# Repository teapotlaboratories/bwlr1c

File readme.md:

# Teapotlabs BWLR1C

Teapotlabs BWLR1C is a wireless LoRa environmental sensor capable of sensing temperature, humidity, air pressure and air quality using the on-board BME680.
This device is an updated to **Teapotlabs BWLR1B,** by using the an on-board antenna.
By using an STM32WLE MCU, the device is capable of multi-year operation before changing the batteries

Teapotlabs BWLR1C is part of  [Teapot open-hardware project](https://github.com/teapotlaboratories).

## Sponsorship
Huge thanks to [PCBWay](https://www.pcbway.com/) to sponsored this project! Most of the project in Teapotlabs from PCB board, PCB Assembly, and 3D Printing is done through their rapid-prototyping services. The process from ordering to delivery of the device was really smooth and easy. We were really happy with the quality of the assembly and especially the customer support that was really easy to work with, where they help us identify and fix issue such as verifying BOM, checking components for assembly and even replacing damaged parts at no cost.

## Disclaimer
- The 1KM range is based on [AERQ - Air Quality Monitoring](https://www.seeedstudio.com/blog/2022/04/27/monitoring-indoor-air-pollutants-the-silent-issue-for-smart-city-iot-using-seeed-lora-e5-and-fusion-pcba/) design, but have not been tested on this device yet
- The position of the BME680 sensor on the board might not be the most efficient

## Future Works
- Change `SW4` wiring from GND to 3V3, to allow booting to STM32WLE USART Bootloader. This enable the user to flash the RAK3172 module using STM32CubeProgrammer without ST-Link.

## Specification

- [RAK3172](https://docs.rakwireless.com/Product-Categories/WisDuo/RAK3172-Module/Overview/): An STM32WLE5CC module
- 3.3V only power/pin. 
- 2uA Deep-Sleep
- BME680 for Environmental Sensing
- Switchable TX Power. 14 dBm(50mA) or 22 dBm(140mA) ( on 915MHz frequency )
- Supports LoRaWAN 1.0.3
- 1KM Range
- UART2 breakout for **Arduino** progamming
- SWD breakout for **Mbed OS/STM32Cube** programming
- SMA antenna connector
- **CR2450** battery holder *xor* **AA** battery holder
- Capacitor ( [optional to prolong CR2450 usage](https://www.rs-online.com/designspark/can-i-prolong-my-coin-cell-battery-life-with-a-capacitor) )

> Based-on [TI's White Paper](https://www.ti.com/lit/wp/swra349/swra349.pdf), using coin-cell to draw short high-power pulses (~40mA) is possible, but will reduce the effective capacity of the battery. The White Paper proposed a solution to increase the effective capacity
## Schematics

## Boards
 <p align="center">  <br><b>PCB Render</b></p>

Built using KiCAD, the board is design to be as small as possible when operated using CR2450 coin-cell batteries

| Top Board | Bottom Board |
|--|--|
|  |  |
|  |  |

 <p align="center"> <br><b>PCB Top and Bottom Layout</b></p> 
  
### Case

Built using [TinkerCAD](https://www.tinkercad.com), the cases are available for the CR2450 variant and the AA variant, 3D printable with any generic 3D printer with/without suppport (depends on the orientation). The STL files are available [here](https://github.com/teapotlaboratories/bwlr1c/tree/main/hardware/case)
 <p align="center"><br><b>Case Open</b></p>

The case is design to be as small as possible with an additional magnets in the back to ease the placement of the sensor. The following are the list of material used at the time of testing:
- 4 piece of 8mm x 2mm neodymium magnet

<p align="center"><br><b>Sensor Placement with Magnet</b></p>

### Measurement
Power consumption and solar charging current are measured using [Nordic PPK2](https://www.nordicsemi.com/Products/Development-hardware/Power-Profiler-Kit-2).
The following are the summary of the measurement:
- Transmit 14dBm:  443ms @ 47mA
- Deep-Sleep : 2 uA

<p align="center"><br><b>Deep-Sleep</b></p>

<p align="center"><br><b>BME688 Measure and LoRa Transmit</b></p>

More measurement can be found [here](https://github.com/teapotlaboratories/bwlr1c/tree/main/docs/measurement)

### Bill Of Materials
Most of the components are generic and can be bought from any electornics/semi-conductor distributor. RAK3172 is the only component available in [RAKwireless store](https://store.rakwireless.com/products/wisduo-lpwan-module-rak3172?variant=40014759493830). The bill of materials can be downloaded [here](https://github.com/teapotlaboratories/bwlr1c/raw/main/hardware/bill_of_materials.csv)

> :warning: **Be sure to buy the RAK3172 variant without IPEX to use the On-Board Antenna** 

|Id |Designator                      |Package                           |Quantity|Designation   |Notes                            |
|---|--------------------------------|----------------------------------|--------|--------------|---------------------------------|
|1  |C5,C12,C11,C3                   |C_1206_3216Metric                 |4       |100nF         |                                 |
|2  |SW4                             |SW_SPST_Omron_B3FS-100xP          |1       |BOOT          |                                 |
|3  |R7,R2,R3,R6                     |R_1206_3216Metric                 |4       |10K           |                                 |
|4  |C9,C8,C10,C2,C4,C13,C14,C6,C1,C7|CP_EIA-3528-15_AVX-H              |10      |330uF         |Optional                         |
|5  |R5                              |R_1206_3216Metric                 |1       |1K            |                                 |
|6  |E1                              |XDCR_ANT-915-USP410               |1       |ANT-915-USP410|                                 |
|7  |SW3                             |SW_SPST_Omron_B3FS-100xP          |1       |RESET         |                                 |
|8  |U1                              |BME680-PSON80P300X300X100-8N      |1       |BME680        |                                 |
|9  |U2                              |RAK3172                           |1       |RAK3172       |                                 |
|10 |Q1                              |SOT-23                            |1       |AO3407        |                                 |
|11 |BT3,BT1                         |BatteryHolder_Keystone_3008_1x2450|2       |CR2450        |Mutual Exclusive with BT2        |
|12 |BT2                             |BatteryHolder_Keystone_2462_2xAA  |1       |2x AA         |Mutual Exclusive with BT3 and BT1|

## Programming
Programming the device can be done over the **UART2** or **SWD**, available next to the On-board antenna.
Out of the factory, the RAK3172 chip ships with an **AT firmware** that can be tested by connecting a USB-to-UART bridge to the **UART2** port.

The following are some very good tutorial to start developing with the device:

- [Communicating with the AT firmware](https://docs.rakwireless.com/Product-Categories/WisDuo/RAK3172-Module/Quickstart/#rak3172-as-a-lora-lorawan-modem-via-at-command)
 - [Programming with Arduino](https://docs.rakwireless.com/Product-Categories/WisDuo/RAK3172-Module/Quickstart/#rak3172-as-a-stand-alone-device-using-rui3)
 - [Programming with STM32Cube](https://docs.rakwireless.com/Product-Categories/WisDuo/RAK3172-Module/Low-Level-Development/#rak3172-on-stm32cubeide-with-stm32wl-sdk-v1-0-0)
 - [Programming with MbedOS](https://github.com/hallard/LoRa-E5-Tiny/blob/main/README.md#compile-and-flash-firmware)

For connecting to the **UART2** port, use any USB-to-UART bridge module. In testing, the [Sparkfun](https://www.sparkfun.com/products/14050) board is used for communication with AT firmware and programming over **Arduino**.
 <p align="center"> <br>Sparkfun USB-to-UART Bridge</p>

> :warning: **Be sure to only use 3.3V module. Do not 5V module** 

For connecting to the **SWD** port, use ST-Link v2  in-circuit debugger and programmer from STM. In testing, ST-Link v2 clone will not work. The ST-Link v2 should atleast be reconizeable by the [STM32CubeProgrammer](https://www.st.com/en/development-tools/stm32cubeprog.html).
A cheap and alternative way to get an authorized ST-Link is to buy a Nucleo board, cut the top part which contain the ST-Link and use it as an external programmer.
 <p align="center"> <br>ST-Link v2 from a Nucleo Development Board</p>
Here are some good tutorial to convert a Nucleo to and external ST-Link v2:

 - https://www.radioshuttle.de/en/turtle-en/nucleo-st-link-interface-en/
 - https://jeelabs.org/book/1547a/index.html

## Notes
There are some issue, notes, and behavior that was discovered at the time of testing and development. The following are those discovery:
- Using Arduino RUI3 framework may introduce some-instability after programming. It is observed that by randomly power-cycling the board in-short interval after flashing, causes the board to hang in Boot mode. The fix is currently on the works.

## Reference
The project won't be possible without the amazing work from people across the globe. The following are the reference to those awesome projects:

 - [LoRa e5 Tiny](https://github.com/hallard/LoRa-E5-Tiny)
 - [AERQ - Air Quality Monitoring](https://www.seeedstudio.com/blog/2022/04/27/monitoring-indoor-air-pollutants-the-silent-issue-for-smart-city-iot-using-seeed-lora-e5-and-fusion-pcba/)

## License
The product is open-source! However, some part of library used under **src**, might have it's own license.
Please reach out or create a ticket to report any license violation.

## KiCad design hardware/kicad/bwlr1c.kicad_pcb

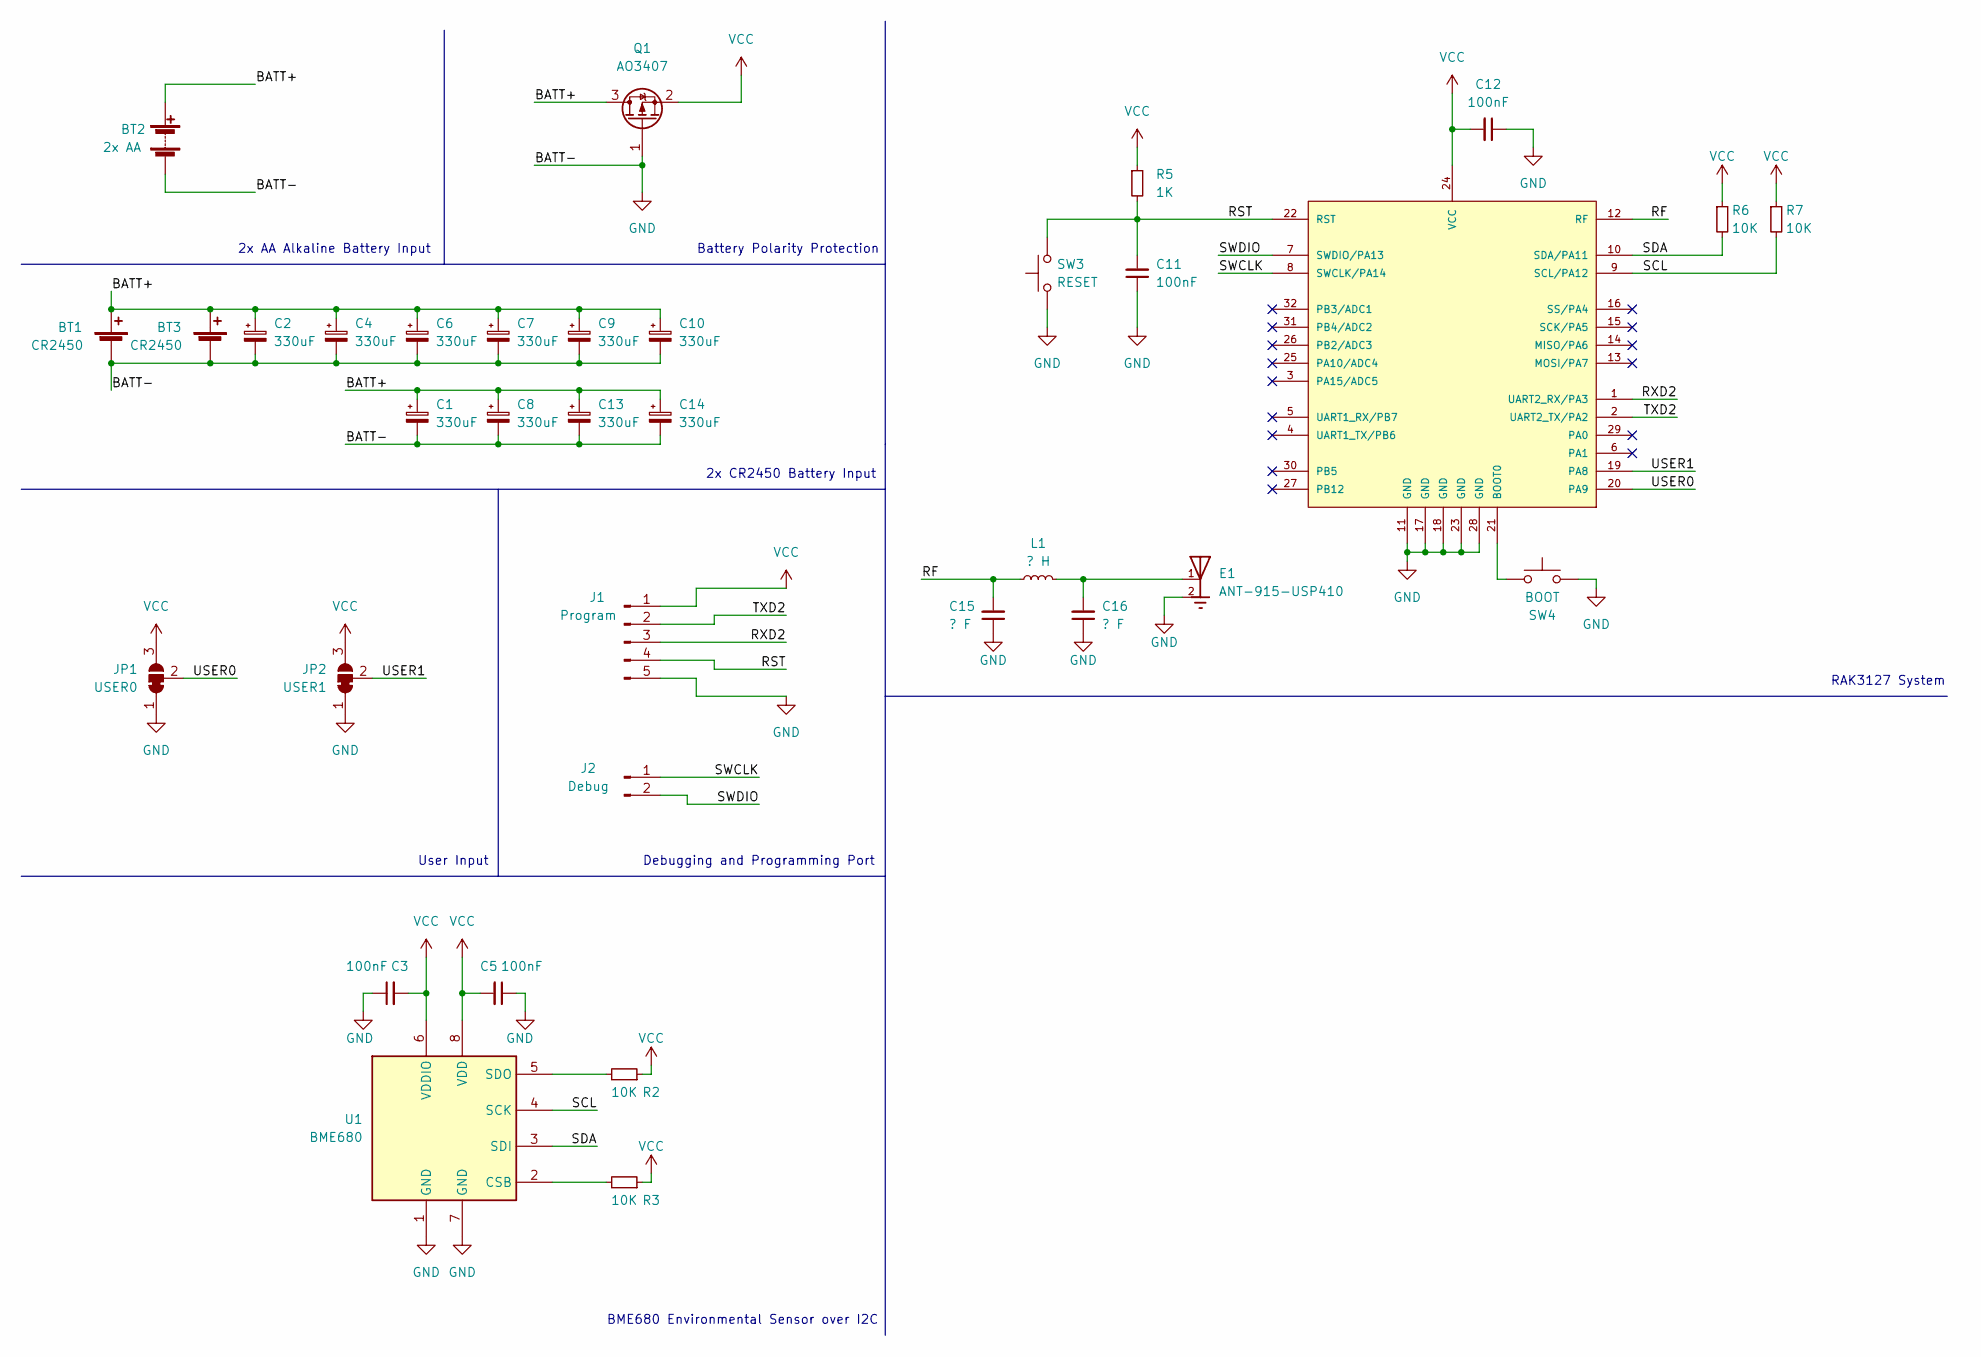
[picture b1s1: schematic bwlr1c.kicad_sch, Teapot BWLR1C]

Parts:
BT1, BT3: CR2450; BatteryHolder_Keystone_3008_1x2450
BT2: 2x AA; BatteryHolder_Keystone_2462_2xAA
C1, C2, C4, C6, C7, C8, C9, C10, C13, C14: 330uF; CP_EIA-3528-15_AVX-H_Pad1.50x2.35mm_HandSolder
C3, C5, C11, C12: 100nF; C_1206_3216Metric_Pad1.33x1.80mm_HandSolder
C15, C16: ? F; C_0603_1608Metric
E1: ANT-915-USP410; XDCR_ANT-915-USP410; PARTREV N/A
J1: Program; PinHeader_1x05_P2.54mm_Vertical
J2: Debug; PinHeader_1x02_P2.54mm_Vertical
JP1: USER0; SolderJumper-3_P1.3mm_Bridged12_RoundedPad1.0x1.5mm_NumberL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
JP2: USER1; SolderJumper-3_P1.3mm_Bridged12_RoundedPad1.0x1.5mm_NumberL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
L1: ? H; L_0603_1608Metric
Q1: AO3407; SOT-23
R2, R3, R6, R7: 10K; R_1206_3216Metric_Pad1.30x1.75mm_HandSolder
R5: 1K; R_1206_3216Metric_Pad1.30x1.75mm_HandSolder
SW3: RESET; SW_SPST_Omron_B3FS-100xP
SW4: BOOT; SW_SPST_Omron_B3FS-100xP
U1: BME680; BME680-PSON80P300X300X100-8N
U2: RAK3172

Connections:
/BATT+: BT1.1 (+), BT2.1 (+), BT3.1 (+), C1.1, C2.1, C4.1, C6.1, C7.1, C8.1, C9.1, C10.1, C13.1, C14.1, Q1.3 (D)
/RF: C15.2, L1.1, U2.12 (RF)
/RST: C11.2, J1.4, R5.2, SW3.2, U2.22 (RST)
/RXD2: J1.3, U2.1 (UART2_RX/PA3)
/SCL: R7.2, U1.4 (SCK), U2.9 (SCL/PA12)
/SDA: R6.2, U1.3 (SDI), U2.10 (SDA/PA11)
/SWCLK: J2.1, U2.8 (SWCLK/PA14)
/SWDIO: J2.2, U2.7 (SWDIO/PA13)
/TXD2: J1.2, U2.2 (UART2_TX/PA2)
/USER0: JP1.2 (C), U2.20 (PA9)
/USER1: JP2.2 (C), U2.19 (PA8)
GND: BT1.2 (-), BT2.2 (-), BT3.2 (-), C1.2, C2.2, C3.1, C4.2, C5.1, C6.2, C7.2, C8.2, C9.2, C10.2, C11.1, C12.1, C13.2, C14.2, C15.1, C16.1, E1.2, J1.5, JP1.1 (A), JP2.1 (A), Q1.1 (G), SW3.1, SW4.2, U1.1 (GND), U1.7 (GND), U2.11 (GND), U2.17 (GND), U2.18 (GND), U2.23 (GND), U2.28 (GND)
unnamed: C16.2, E1.1, L1.2
unnamed: R2.2, U1.5 (SDO)
unnamed: R3.2, U1.2 (CSB)
unnamed: SW4.1, U2.21 (BOOT0)
VCC: C3.2, C5.2, C12.2, J1.1, JP1.3 (B), JP2.3 (B), Q1.2 (S), R2.1, R3.1, R5.1, R6.1, R7.1, U1.6 (VDDIO), U1.8 (VDD), U2.24 (VCC)

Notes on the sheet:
RAK3127 System
BME680 Environmental Sensor over I2C
2x CR2450 Battery Input
Battery Polarity Protection
2x AA Alkaline Battery Input
User Input
Debugging and Programming Port

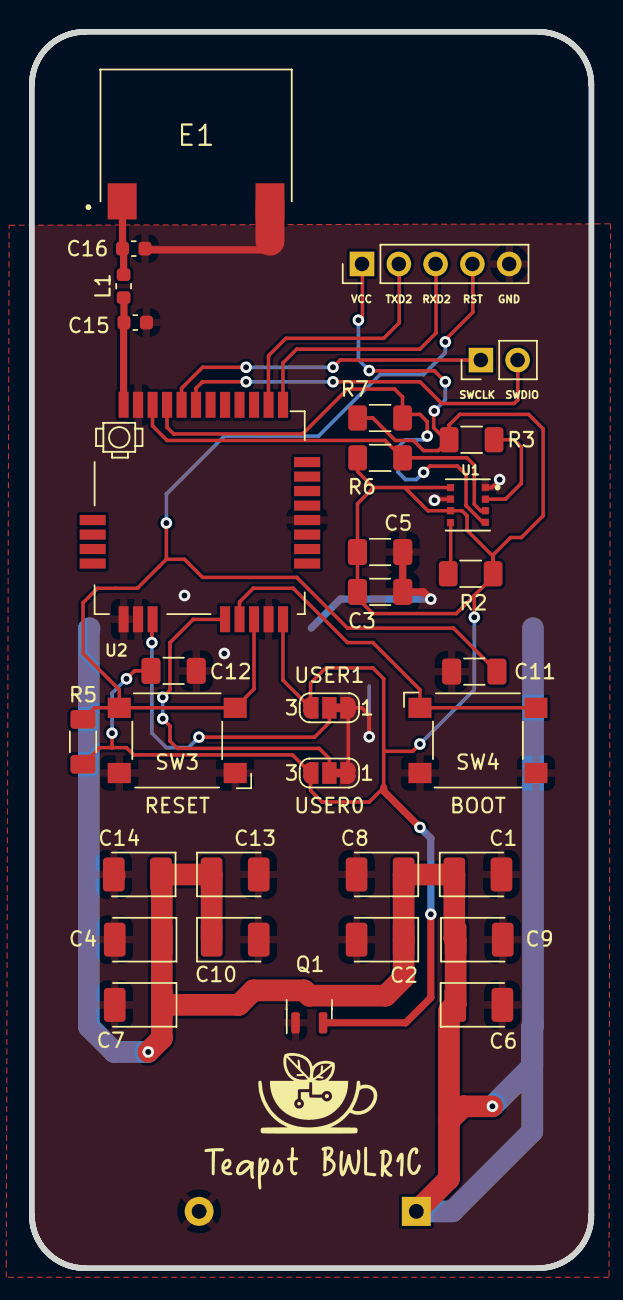
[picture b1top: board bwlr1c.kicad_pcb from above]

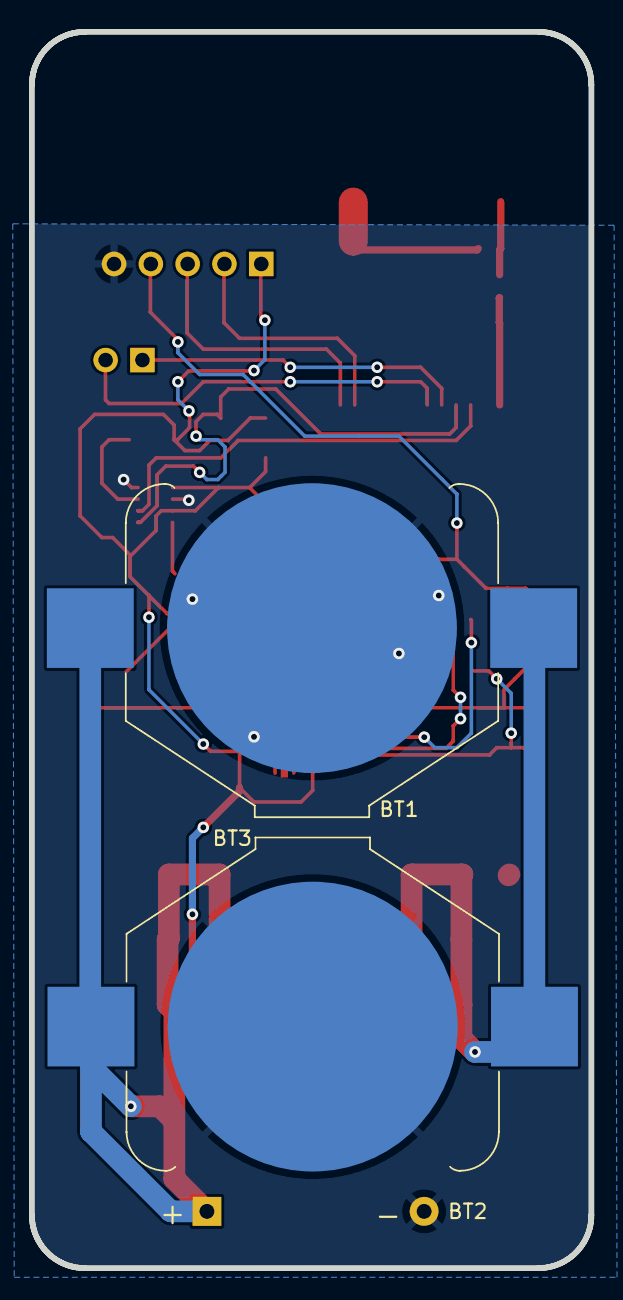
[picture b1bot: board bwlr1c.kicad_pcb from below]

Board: 2 copper layers, 38.6 x 85.3 mm, 35 parts (3 on the bottom side), 17 nets.

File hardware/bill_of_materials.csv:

Id,Designator,Package,Quantity,Designation,Notes
1,"C5,C12,C11,C3",C_1206_3216Metric,4,100nF,
2,SW4,SW_SPST_Omron_B3FS-100xP,1,BOOT,
3,"R7,R2,R3,R6",R_1206_3216Metric,4,10K,
4,"C9,C8,C10,C2,C4,C13,C14,C6,C1,C7",CP_EIA-3528-15_AVX-H,10,330uF,Optional
5,R5,R_1206_3216Metric,1,1K,
6,E1,XDCR_ANT-915-USP410,1,ANT-915-USP410,
7,SW3,SW_SPST_Omron_B3FS-100xP,1,RESET,
8,U1,BME680-PSON80P300X300X100-8N,1,BME680,
9,U2,RAK3172,1,RAK3172,
10,Q1,SOT-23,1,AO3407,
11,"BT3,BT1",BatteryHolder_Keystone_3008_1x2450,2,CR2450,Mutual Exclusive with BT2
12,BT2,BatteryHolder_Keystone_2462_2xAA,1,2x AA,Mutual Exclusive with BT3 and BT1

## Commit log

2022-08-25 add library
2022-08-26 upload resources
2022-08-26 move images
2022-08-26 upload supporting images
2022-08-26 add readme
2022-08-26 add src
2022-09-03 update library
2022-09-03 update footprint and library
2024-11-27 add sponsorship message

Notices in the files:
readme.md:
License:
License: MIT
